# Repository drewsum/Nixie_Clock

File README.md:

# Nixie_Clock

Rev B Hardware designed with KiCad 7.0.1

Rev B MCU Firmware written with MPLAB X IDE v6.15, compiled with Microchip XC32 2.30 Compiler - NOT COMPATIBLE with newer compiler versions (4.30)

## Rev A Readme:
A nixie clock designed around a PIC16LF1519

Programming notes: PIC16LF1519 (U501) is programmed through PICKIT3 interface header (J501). Firmware included in GIT repository should already be built and the hex file can be programmed directly into the flash on the PIC. If you wish to build it yourself, use Microchip's XC8 compiler, and ensure that the User ID bytes located in NVM match the expected_user_ID[] byte array saved in RAM. The values programmed into NVM are set in /mcc_generated_files/mcc.c, and are set with the line #pragma config IDLOCx = _ . Reference page 44 of the PIC16LF1519 datasheet. If you don't feel like altering user ID's, leave them unchanged in source code, and just build it as is. If user IDs and device IDs do not match, the clock will brick itself until reprogrammed with matching values.

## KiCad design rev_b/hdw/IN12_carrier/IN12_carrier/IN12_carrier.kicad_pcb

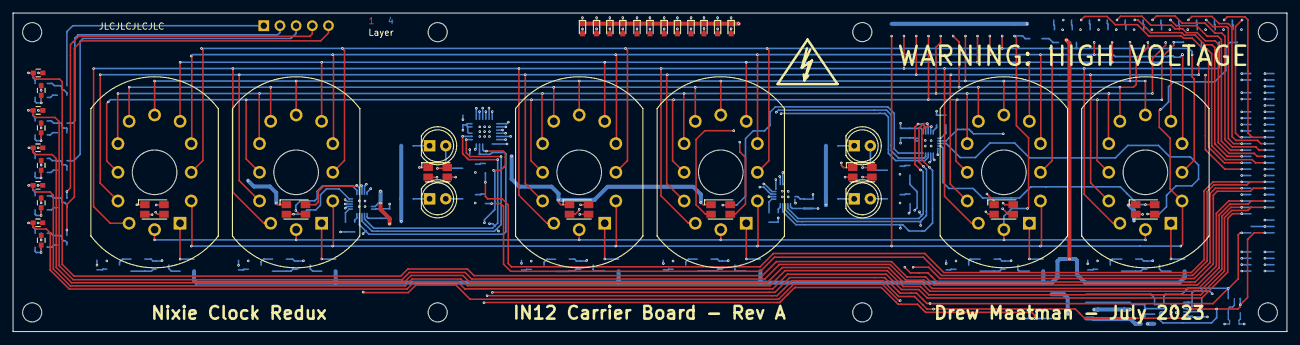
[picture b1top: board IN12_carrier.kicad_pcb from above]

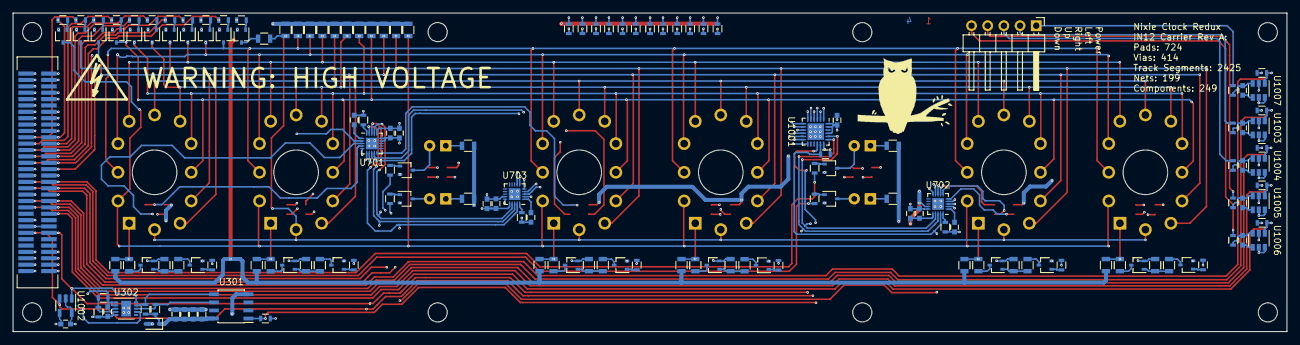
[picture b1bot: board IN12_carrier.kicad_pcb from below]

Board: 4 copper layers, 200.0 x 50.0 mm, 203 parts (155 on the bottom side), 172 nets.

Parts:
C301, C302, C303, C701, C702, C703, C704, C705, C706: 10uF; C_0603
C304, C305, C707, C708, C709, C1001, C1002, C1003, C1004, C1005, C1006, C1011, C1012, C1013, C1014, C1015, C1017: 0.1uF; C_0603
C1007, C1008, C1009, C1010, C1016: 10nF; C_0603
D301: BAT48JFILM; D_SOD-323
D701, D702, D703, D704, D705, D706, D707, D708: ASMB-MTB0-0A3A2; LED_Avago_PLCC4_3.2x2.8mm_CW
D901, D1001, D1002, D1003, D1004, D1005, D1006, D1007, D1008, D1009, D1010, D1011: Orange; LED_0603
H1201, H1202, H1203, H1204, H1205, H1206, H1207, H1208: MountingHole; MountingHole_3mm
J201: Conn_02x32_Top_Bottom; CONN_5120528-1_TYC
J1001: Cap SNS; PinHeader_1x05_P2.54mm_Horizontal
Q401, Q402, Q403, Q407, Q408, Q409, Q501, Q502, Q503, Q504, Q505, Q506, Q507, Q508, Q509, Q510, Q511, Q512, Q513, Q514, Q515: MMSTA42; SOT-323_SC-70
Q404, Q405, Q406, Q410, Q411, Q412: MMSTA92; SOT-323_SC-70
R301, R302, R305, R401, R402, R403, R413, R414, R415, R501, R502, R503, R504, R505, R506, R507, R508, R509, R510, R511, R512, R513, R515, R516, R701, R1012, R1013, R1014, R1015, R1020: 10k; R_0603
R303: 392k; R_0603
R304: 1M; R_0603
R404, R405, R406, R416, R417, R418, R801, R802, R803, R804, R805, R806, R807, R808, R809, R810, R811, R812, R813, R814, R815, R816, R817: 470k; R_0805
R407, R408, R409, R419, R420, R421: 100k; R_0805
R410, R411, R412, R422, R423, R424, R514: 18k; R_0805
R601, R602, R603, R604: 10k; R_0805
R704, R705, R706: 3.65k; R_0603
R901, R1001, R1002, R1003, R1004, R1005, R1006, R1007, R1008, R1009, R1010, R1011, R1016, R1017, R1018, R1019, R1021: 499; R_0603
U301: DS1683; SOIC-8_3.9x4.9mm_Pitch1.27mm
U302: LTC4316DD; DFN-10-1EP_3x3mm_Pitch0.5mm
U701, U702, U703: LP5009; UQFN-20-1EP_3x3mm_Pitch0.4mm
U1001: TCA9555RGER; QFN-24-1EP_4x4mm_P0.5mm_EP2.6x2.6mm
U1002: 24AA02-OT; SOT-23-5
U1003, U1004, U1005, U1006, U1007: AT42QT1010-TSHR; SOT-23-6
V601, V602, V603, V604, V605, V608: IN12B; IN-12B
V606, V607, V609, V610: IN3; LED_D5.0mm

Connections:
24HR_Mode_LED: R1010.1, U1001.11
+3.3V: C305.1, C704.1, C705.1, C706.1, C707.1, C708.1, C709.1, C1001.1, C1002.1, C1011.1, C1012.1, C1013.1, C1014.1, C1017.1, D301.2 (A), D701.1 (A), D702.1 (A), D703.1 (A), D704.1 (A), D705.1 (A), D706.1 (A), D707.1 (A), D708.1 (A), J201.61, J201.62, J201.63, J201.64, R304.1, U302.4 (VCC), U302.5 (Enable), U701.16 (VCC), U702.14 (ADDR0), U702.16 (VCC), U703.15 (ADDR1), U703.16 (VCC), U1001.18 (A0), U1001.21 (VCC), U1001.23 (A1), U1001.24 (A2), U1002.4 (V_{CC}), U1003.5 (VDD), U1003.6 (SYNC), U1004.5 (VDD), U1004.6 (SYNC), U1005.5 (VDD), U1005.6 (SYNC), U1006.5 (VDD), U1006.6 (SYNC), U1007.5 (VDD), U1007.6 (SYNC)
+90V: J201.33, J201.34, R801.2, R802.2, R803.2, R804.2, R805.2, R806.2, R807.2, R808.2, R809.2, R810.2, R811.2, R812.2, R813.2, R814.2, R815.2, R816.2, R817.2
+180V: J201.36, J201.37, Q404.2 (E), Q405.2 (E), Q406.2 (E), Q410.2 (E), Q411.2 (E), Q412.2 (E), R407.2, R408.2, R409.2, R419.2, R420.2, R421.2, R601.1, R602.1, R603.1, R604.1
Alarm_Enable_LED: R1009.1, U1001.10
Anode_0: R410.1, R801.1, V604.1 (Anode)
Anode_0_DSP: J201.39, R401.1
Anode_1: R422.1, R802.1, V602.1 (Anode)
Anode_1_DSP: J201.7, R413.1
Anode_2: R411.1, R803.1, V608.1 (Anode)
Anode_2_DSP: J201.40, R402.1
Anode_3: R423.1, R804.1, V605.1 (Anode)
Anode_3_DSP: J201.8, R414.1
Anode_4: R412.1, R805.1, V603.1 (Anode)
Anode_4_DSP: J201.41, R403.1
Anode_5: R424.1, R806.1, V601.1 (Anode)
Anode_5_DSP: J201.9, R415.1
COLON0_LED_B: D703.2 (BK), U703.4 (OUT2)
COLON0_LED_G: D703.3 (GK), U703.3 (OUT1)
COLON0_LED_R: D703.4 (RK), U703.2 (OUT0)
COLON1_LED_B: D706.2 (BK), U703.7 (OUT5)
COLON1_LED_G: D706.3 (GK), U703.6 (OUT4)
COLON1_LED_R: D706.4 (RK), U703.5 (OUT3)
Cathode_0: Q501.3 (C), R807.1, V601.2 (Digit0), V602.2 (Digit0), V603.2 (Digit0), V604.2 (Digit0), V605.2 (Digit0), V608.2 (Digit0)
Cathode_0_DSP: J201.43, R501.1
Cathode_1: Q506.3 (C), R808.1, V601.11 (Digit1), V602.11 (Digit1), V603.11 (Digit1), V604.11 (Digit1), V605.11 (Digit1), V608.11 (Digit1)
Cathode_1_DSP: J201.11, R506.1
Cathode_2: Q502.3 (C), R809.1, V601.10 (Digit2), V602.10 (Digit2), V603.10 (Digit2), V604.10 (Digit2), V605.10 (Digit2), V608.10 (Digit2)
Cathode_2_DSP: J201.44, R502.1
Cathode_3: Q507.3 (C), R810.1, V601.9 (Digit3), V602.9 (Digit3), V603.9 (Digit3), V604.9 (Digit3), V605.9 (Digit3), V608.9 (Digit3)
Cathode_3_DSP: J201.12, R507.1
Cathode_4: Q503.3 (C), R811.1, V601.8 (Digit4), V602.8 (Digit4), V603.8 (Digit4), V604.8 (Digit4), V605.8 (Digit4), V608.8 (Digit4)
Cathode_4_DSP: J201.45, R503.1
Cathode_5: Q508.3 (C), R812.1, V601.7 (Digit5), V602.7 (Digit5), V603.7 (Digit5), V604.7 (Digit5), V605.7 (Digit5), V608.7 (Digit5)
Cathode_5_DSP: J201.13, R508.1
Cathode_6: Q504.3 (C), R813.1, V601.6 (Digit6), V602.6 (Digit6), V603.6 (Digit6), V604.6 (Digit6), V605.6 (Digit6), V608.6 (Digit6)
Cathode_6_DSP: J201.46, R504.1
Cathode_7: Q509.3 (C), R814.1, V601.5 (Digit7), V602.5 (Digit7), V603.5 (Digit7), V604.5 (Digit7), V605.5 (Digit7), V608.5 (Digit7)
Cathode_7_DSP: J201.14, R509.1
Cathode_8: Q505.3 (C), R815.1, V601.4 (Digit8), V602.4 (Digit8), V603.4 (Digit8), V604.4 (Digit8), V605.4 (Digit8), V608.4 (Digit8)
Cathode_8_DSP: J201.47, R505.1
Cathode_9: Q510.3 (C), R816.1, V601.3 (Digit9), V602.3 (Digit9), V603.3 (Digit9), V604.3 (Digit9), V605.3 (Digit9), V608.3 (Digit9)
Cathode_9_DSP: J201.15, R510.1
Cathode_DP: R514.2, R817.1, V601.12 (DP), V602.12 (DP), V603.12 (DP), V604.12 (DP), V605.12 (DP), V608.12 (DP)
Cathode_DP_DSP: J201.48, R511.1
Colon_0_Cathode: Q513.3 (C), V606.2 (Kathode)
Colon_0_DSP: J201.50, R513.1
Colon_1_Cathode: Q512.3 (C), V607.2 (Kathode)
Colon_1_DSP: J201.18, R512.1
Colon_2_Cathode: Q515.3 (C), V609.2 (Kathode)
Colon_2_DSP: J201.51, R516.1
Colon_3_Cathode: Q514.3 (C), V610.2 (Kathode)
Colon_3_DSP: J201.19, R515.1
Display_Alarm_LED: R1007.1, U1001.7 (P06)
Display_Date_LED: R1003.1, U1001.3 (P02)
Display_Time_LED: R1001.1, U1001.1 (P00)
Display_Weekday_LED: R1005.1, U1001.5 (P04)
GND: C301.2, C302.2, C303.2, C304.2, C305.2, C701.2, C702.2, C703.2, C704.2, C705.2, C706.2, C707.2, C708.2, C709.2, C1001.2, C1002.2, C1003.2, C1004.2, C1005.2, C1006.2, C1011.2, C1012.2, C1013.2, C1014.2, C1015.2, C1017.2, D901.1 (K), D1001.1 (K), D1002.1 (K), D1003.1 (K), D1004.1 (K), D1005.1 (K), D1006.1 (K), D1007.1 (K), D1008.1 (K), D1009.1 (K), D1010.1 (K), D1011.1 (K), J201.1, J201.2, J201.3, J201.4, J201.5, J201.6, J201.10, J201.16, J201.17, J201.20, J201.24, J201.25, J201.29, J201.30, J201.31, J201.32, J201.42, J201.49, J201.52, J201.57, Q401.2 (E), Q402.2 (E), Q403.2 (E), Q407.2 (E), Q408.2 (E), Q409.2 (E), Q501.2 (E), Q502.2 (E), Q503.2 (E), Q504.2 (E), Q505.2 (E), Q506.2 (E), Q507.2 (E), Q508.2 (E), Q509.2 (E), Q510.2 (E), Q511.2 (E), Q512.2 (E), Q513.2 (E), Q514.2 (E), Q515.2 (E), R303.2, R305.2, R701.2, R704.2, R705.2, R706.2, R1012.2, R1013.2, R1014.2, R1015.2, R1020.2, U301.4 (GND), U302.1 (GND), U302.2 (XORH), U302.11 (GND), U701.14 (ADDR0), U701.15 (ADDR1), U701.21 (GND), U702.15 (ADDR1), U702.21 (GND), U703.14 (ADDR0), U703.21 (GND), U1001.9 (GND), U1001.25 (EPAD), U1002.2 (V_{SS}), U1002.5 (WP), U1003.2 (VSS), U1004.2 (VSS), U1005.2 (VSS), U1006.2 (VSS), U1007.2 (VSS)
I2C_DSP_SCL: J201.58, U302.10 (SCLIN), U701.18 (SCL), U702.18 (SCL), U703.18 (SCL), U1001.19 (SCL), U1002.1 (SCL)
I2C_DSP_SDA: J201.26, U302.7 (SDAIN), U701.17 (SDA), U702.17 (SDA), U703.17 (SDA), U1001.20 (SDA), U1002.3 (SDA)
unnamed: C301.1, C302.1, C303.1, C304.1, D301.1 (K), R301.1, R302.1, U301.8 (VCC)
unnamed: D901.2 (A), R901.2
unnamed: D1001.2 (A), R1001.2
unnamed: D1002.2 (A), R1002.2
unnamed: D1003.2 (A), R1003.2
unnamed: D1004.2 (A), R1004.2
unnamed: D1005.2 (A), R1005.2
unnamed: D1006.2 (A), R1006.2
unnamed: D1007.2 (A), R1007.2
unnamed: D1008.2 (A), R1008.2
unnamed: D1009.2 (A), R1009.2
unnamed: D1010.2 (A), R1010.2
unnamed: D1011.2 (A), R1011.2
unnamed: Q401.1 (B), R401.2
unnamed: Q401.3 (C), R404.1
unnamed: Q402.1 (B), R402.2
unnamed: Q402.3 (C), R405.1
unnamed: Q403.1 (B), R403.2
unnamed: Q403.3 (C), R406.1
unnamed: Q404.1 (B), R404.2, R407.1
unnamed: Q404.3 (C), R410.2
unnamed: Q405.1 (B), R405.2, R408.1
unnamed: Q405.3 (C), R411.2
unnamed: Q406.1 (B), R406.2, R409.1
unnamed: Q406.3 (C), R412.2
unnamed: Q407.1 (B), R413.2
unnamed: Q407.3 (C), R416.1
unnamed: Q408.1 (B), R414.2
unnamed: Q408.3 (C), R417.1
unnamed: Q409.1 (B), R415.2
unnamed: Q409.3 (C), R418.1
unnamed: Q410.1 (B), R416.2, R419.1
unnamed: Q410.3 (C), R422.2
unnamed: Q411.1 (B), R417.2, R420.1
unnamed: Q411.3 (C), R423.2
unnamed: Q412.1 (B), R418.2, R421.1
unnamed: Q412.3 (C), R424.2
unnamed: Q501.1 (B), R501.2
unnamed: Q502.1 (B), R502.2
unnamed: Q503.1 (B), R503.2
unnamed: Q504.1 (B), R504.2
unnamed: Q505.1 (B), R505.2
unnamed: Q506.1 (B), R506.2
unnamed: Q507.1 (B), R507.2
unnamed: Q508.1 (B), R508.2
unnamed: Q509.1 (B), R509.2
unnamed: Q510.1 (B), R510.2
unnamed: Q511.1 (B), R511.2
unnamed: Q511.3 (C), R514.1
unnamed: Q512.1 (B), R512.2
unnamed: Q513.1 (B), R513.2
unnamed: Q514.1 (B), R515.2
unnamed: Q515.1 (B), R516.2
unnamed: R301.2, U301.5 (SCL), U302.9 (SCLOUT)
unnamed: R302.2, U301.6 (SDA), U302.8 (SDAOUT)
unnamed: R303.1, R304.2, U302.3 (XORL)
unnamed: R704.1, U701.20 (IREF)
unnamed: C701.1, U701.1 (VCAP)
unnamed: R705.1, U702.20 (IREF)
unnamed: C702.1, U702.1 (VCAP)
unnamed: R706.1, U703.20 (IREF)
unnamed: C703.1, U703.1 (VCAP)
unnamed: C1007.1, U1003.4 (SNS)
unnamed: C1007.2, R1016.2, U1003.3 (SNSK)
unnamed: C1008.1, U1004.4 (SNS)
unnamed: C1008.2, R1017.2, U1004.3 (SNSK)
unnamed: C1009.1, U1005.4 (SNS)
unnamed: C1009.2, R1018.2, U1005.3 (SNSK)
unnamed: C1010.1, U1006.4 (SNS)
unnamed: C1010.2, R1019.2, U1006.3 (SNSK)
unnamed: C1016.1, U1007.4 (SNS)
unnamed: C1016.2, R1021.2, U1007.3 (SNSK)
unnamed: R601.2, V606.1 (Anode)
unnamed: R602.2, V607.1 (Anode)
unnamed: R603.2, V609.1 (Anode)
unnamed: R604.2, V610.1 (Anode)
Pushbutton_Down: C1005.1, J201.55, R1014.1, U1006.1 (OUT)
Pushbutton_Down_SNS: J1001.5, R1019.1
Pushbutton_Left: C1015.1, J201.21, R1020.1, U1003.1 (OUT)
Pushbutton_Left_SNS: J1001.2, R1016.1
Pushbutton_Power: C1006.1, J201.53, R1015.1, U1007.1 (OUT)
Pushbutton_Power_SNS: J1001.1, R1021.1
Pushbutton_Right: C1003.1, J201.54, R1012.1, U1004.1 (OUT)
Pushbutton_Right_SNS: J1001.3, R1017.1
Pushbutton_Up: C1004.1, J201.22, R1013.1, U1005.1 (OUT)
Pushbutton_Up_SNS: J1001.4, R1018.1
Set_Alarm_LED: R1008.1, U1001.8 (P07)
Set_Brightness_LED: R1011.1, U1001.12
Set_Color_LED: R901.1, U1001.13
Set_Date_LED: R1004.1, U1001.4 (P03)
Set_Time_LED: R1002.1, U1001.2 (P01)
Set_Weekday_LED: R1006.1, U1001.6 (P05)
TUBE0_LED_B: D701.2 (BK), U701.4 (OUT2)
TUBE0_LED_G: D701.3 (GK), U701.3 (OUT1)
TUBE0_LED_R: D701.4 (RK), U701.2 (OUT0)
TUBE1_LED_B: D704.2 (BK), U701.7 (OUT5)
TUBE1_LED_G: D704.3 (GK), U701.6 (OUT4)
TUBE1_LED_R: D704.4 (RK), U701.5 (OUT3)
TUBE2_LED_B: D707.2 (BK), U701.10 (OUT8)
TUBE2_LED_G: D707.3 (GK), U701.9 (OUT7)
TUBE2_LED_R: D707.4 (RK), U701.8 (OUT6)
TUBE3_LED_B: D702.2 (BK), U702.4 (OUT2)
TUBE3_LED_G: D702.3 (GK), U702.3 (OUT1)
TUBE3_LED_R: D702.4 (RK), U702.2 (OUT0)
TUBE4_LED_B: D705.2 (BK), U702.7 (OUT5)
TUBE4_LED_G: D705.3 (GK), U702.6 (OUT4)
TUBE4_LED_R: D705.4 (RK), U702.5 (OUT3)
TUBE5_LED_B: D708.2 (BK), U702.10 (OUT8)
TUBE5_LED_G: D708.3 (GK), U702.9 (OUT7)
TUBE5_LED_R: D708.4 (RK), U702.8 (OUT6)
Tube_ETC_Enable: R305.1, U301.1 (EVENT), U1001.16
Tube_LED_Enable: R701.1, U701.19 (EN), U702.19 (EN), U703.19 (EN), U1001.17

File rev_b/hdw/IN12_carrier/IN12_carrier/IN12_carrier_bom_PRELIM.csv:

Component,Description,Part,References,Value,Configuration,Footprint,Quantity Per PCB,,,Digi-Key PN,Voltage,display_footprint,Footprint Display,Tolerance,Wattage
1,Unpolarized capacitor,C_Custom,C1007 C1008 C1009 C1010 C1016,10nF,,C_0603,5,,,1276-1009-1-ND,50V,603,,,
2,Unpolarized capacitor,C_Custom,C707 C708 C709 C1001 C1002 C1003 C1004 C1005 C1006 C1011 C1012 C1013 C1014 C1015 C1017,0.1uF,,C_0603,15,,,1276-CL10B104KB8NNNLCT-ND,50V,603,,,
3,,C_Custom,C304 C305,0.1uF,ETC,C_0603,2,,,1276-CL10B104KB8NNNLCT-ND,50V,603,,,
4,,C_Custom,C301 C302 C303,10uF,ETC,C_0603,3,,,1276-1871-1-ND,10V,603,,,
5,Unpolarized capacitor,C_Custom,C701 C702 C703 C704 C705 C706,10uF,,C_0603,6,,,1276-1871-1-ND,10V,603,,,
6,"Tricolor Black Surface LED, Common Anode Pin 1, PLCC-4",ASMB-MTB0-0A3A2,D701 D702 D703 D704 D705 D706 D707 D708,ASMB-MTB0-0A3A2,,LED_Avago_PLCC4_3.2x2.8mm_CW,8,,,516-3279-1-ND,,,,,
7,Light emitting diode,LED,D901 D1001 D1002 D1003 D1004 D1005 D1006 D1007 D1008 D1009 D1010 D1011,Amber,,LED_0603,12,,,732-150060AS75000CT-ND,,,,,
8,"40V 0.35A Small Signal Schottky Diode, SOD-323",BAT48JFILM,D301,BAT48JFILM,ETC,D_SOD-323,1,,,497-5711-1-ND,,,,,
,,,,,,,,,,,,,,,
,,,,,,,,,,,,,,,
,,,,,,,,,,,,,,,
,,,,,,,,,,,,,,,
,,,,,,,,,,,,,,,
,,,,,,,,,,,,,,,
,,,,,,,,,,,,,,,
16,"Generic connector, double row, 02x32, top/bottom pin numbering scheme (row 1: 1...pins_per_row, row2: pins_per_row+1 ... num_pins), script generated (kicad-library-utils/schlib/autogen/connector/)",Conn_02x32_Top_Bottom,J201,Conn_02x32_Top_Bottom,,CONN_5120528-1_TYC,1,,,A104089CT-ND,,,,,
17,,Screw,MK1107 MK1108 MK1115 MK1116 MK1123 MK1124 MK1131 MK1132 MK1133 MK1134 MK1135 MK1136 MK1137 MK1138 MK1139 MK1140,Screw,,,16,,,36-9900-ND,,,,,
18,,Standoff,MK1101 MK1102 MK1103 MK1104 MK1105 MK1106 MK1109 MK1110 MK1111 MK1112 MK1113 MK1114 MK1117 MK1118 MK1119 MK1120 MK1121 MK1122 MK1125 MK1126 MK1127 MK1128 MK1129 MK1130,Standoff,,,24,,,1772-2080-ND 1772-1220-ND,,,,,
19,,Q_NPN_BEC,Q401 Q402 Q403 Q407 Q408 Q409 Q501 Q502 Q503 Q504 Q505 Q506 Q507 Q508 Q509 Q510 Q511 Q512 Q513 Q514 Q515,MMSTA42,,SOT-323_SC-70,21,,,MMSTA42-FDICT-ND,,,SOT-323,,
20,,Q_PNP_BEC,Q404 Q405 Q406 Q410 Q411 Q412,MMSTA92,,SOT-323_SC-70,6,,,MMSTA92-TPCT-ND,,,SOT-323,,
21,Resistor,R_Custom,R901 R1001 R1002 R1003 R1004 R1005 R1006 R1007 R1008 R1009 R1010 R1011 R1016 R1017 R1018 R1019 R1021,499,,R_0603,17,,,541-CRCW0603499RFKEBCT-ND,,603,,1%,1/10W
22,Resistor,R_Custom,R704 R705 R706,3.65k,,R_0603,3,,,541-3.65KHCT-ND,,603,,1%,1/10W
23,Resistor,R_Custom,R701 R1012 R1013 R1014 R1015 R1020,10k,,R_0603,6,,,541-10.0KHCT-ND,,603,,1%,1/10W
24,Resistor,R_Custom,R301 R302 R305,10k,ETC,R_0603,3,,,541-10.0KHCT-ND,,603,,1%,1/10W
25,Resistor,R_Custom,R401 R402 R403 R413 R414 R415 R501 R502 R503 R504 R505 R506 R507 R508 R509 R510 R511 R512 R513 R515 R516,10k,,R_0603,21,,,541-10.0KHCT-ND,,603,,1%,1/10W
26,,R,R601 R602 R603 R604,10k,,R_0805,4,,,541-3015-1-ND,,805,,1%,1/10W
27,Resistor,R_Custom,R410 R411 R412 R422 R423 R424 R514,18k,,R_0805,7,,,541-18.0KCCT-ND,,805,,1%,1/8W
28,Resistor,R_Custom,R407 R408 R409 R419 R420 R421,100k,,R_0805,6,,,541-4318-1-ND,,805,,1%,1/8W
29,Resistor,R_Custom,R303,392k,ETC,R_0603,1,,,541-392KHCT-ND,,603,,1%,1/10W
30,Resistor,R_Custom,R404 R405 R406 R416 R417 R418 R801 R802 R803 R804 R805 R806 R807 R808 R809 R810 R811 R812 R813 R814 R815 R816 R817,470k,,R_0805,23,,,541-470KCCT-ND Digi-Key PN: 541-470KCCT-ND,,805,,1%,1/8W
31,Resistor,R_Custom,R304,1M,ETC,R_0603,1,,,541-2990-1-ND,,603,,1%,1/10W
32,"I2C Serial EEPROM, 2Kb, SOT-23",24AA02-OT,U1002,24AA02-OT,,SOT-23-5,1,,,24AA02E64T-I/OT,,,,,
33,"Single-key Touch Sensor, SOT-23-6",AT42QT1010-TSHR,U1003 U1004 U1005 U1006 U1007,AT42QT1010-TSHR,,SOT-23-6,5,,,AT42QT1010-TSHRCT-ND,,,,,
34,,DS1683,U301,DS1683,ETC,SOIC-8_3.9x4.9mm_Pitch1.27mm,1,,,DS1683S+-ND,,,,,
35,"LP50xx 9-Channel, 12-Bit PWM Ultra-low Quiescent Current I2C RGB LED Drivers",LP5009,U701 U702 U703,LP5009,,UQFN-20-1EP_3x3mm_Pitch0.4mm,3,,,296-LP5009RUKRCT-ND,,,,,
36,Single I2C/SMBUS Address Translator,LTC4316DD,U302,LTC4316DD,ETC,DFN-10-1EP_3x3mm_Pitch0.5mm,1,,,LTC4316IDD#PBF-ND,,,,,
37,"16-bit I/O expander, I2C and SMBus interface, interrupts, w/ pull-ups, QFN-24",TCA9555RGER,U1001,TCA9555RGER,,QFN-24-1EP_4x4mm_P0.5mm_EP2.6x2.6mm,1,,,296-44537-1-ND,,,,,
38,,IN12B,V601 V602 V603 V604 V605 V608,IN12B,,IN-12B,6,,,,,,,,
39,,IN3,V606 V607 V609 V610,IN3,,LED_D5.0mm,4,,,,,,,,

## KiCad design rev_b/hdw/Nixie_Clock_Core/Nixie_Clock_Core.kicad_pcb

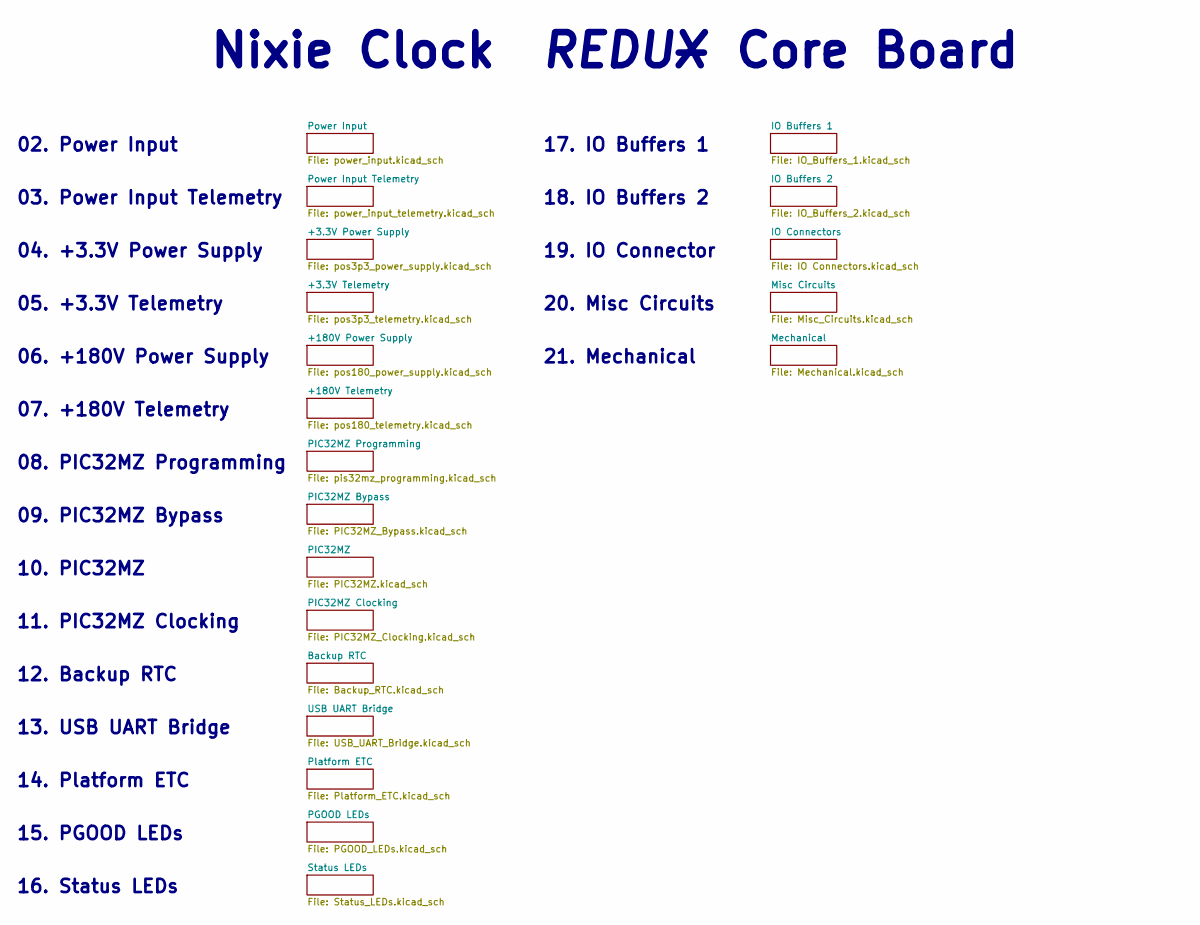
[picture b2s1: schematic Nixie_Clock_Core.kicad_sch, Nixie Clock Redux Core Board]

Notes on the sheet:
04. +3.3V Power Supply
Nixie Clock - Core Board
12. Backup RTC
20. Misc Circuits
02. Power Input
11. PIC32MZ Clocking
09. PIC32MZ Bypass
06. +180V Power Supply
17. IO Buffers 1
08. PIC32MZ Programming
07. +180V Telemetry
13. USB UART Bridge
16. Status LEDs
15. PGOOD LEDs
REDUX
21. Mechanical
18. IO Buffers 2
05. +3.3V Telemetry
14. Platform ETC
03. Power Input Telemetry
19. IO Connector
10. PIC32MZ

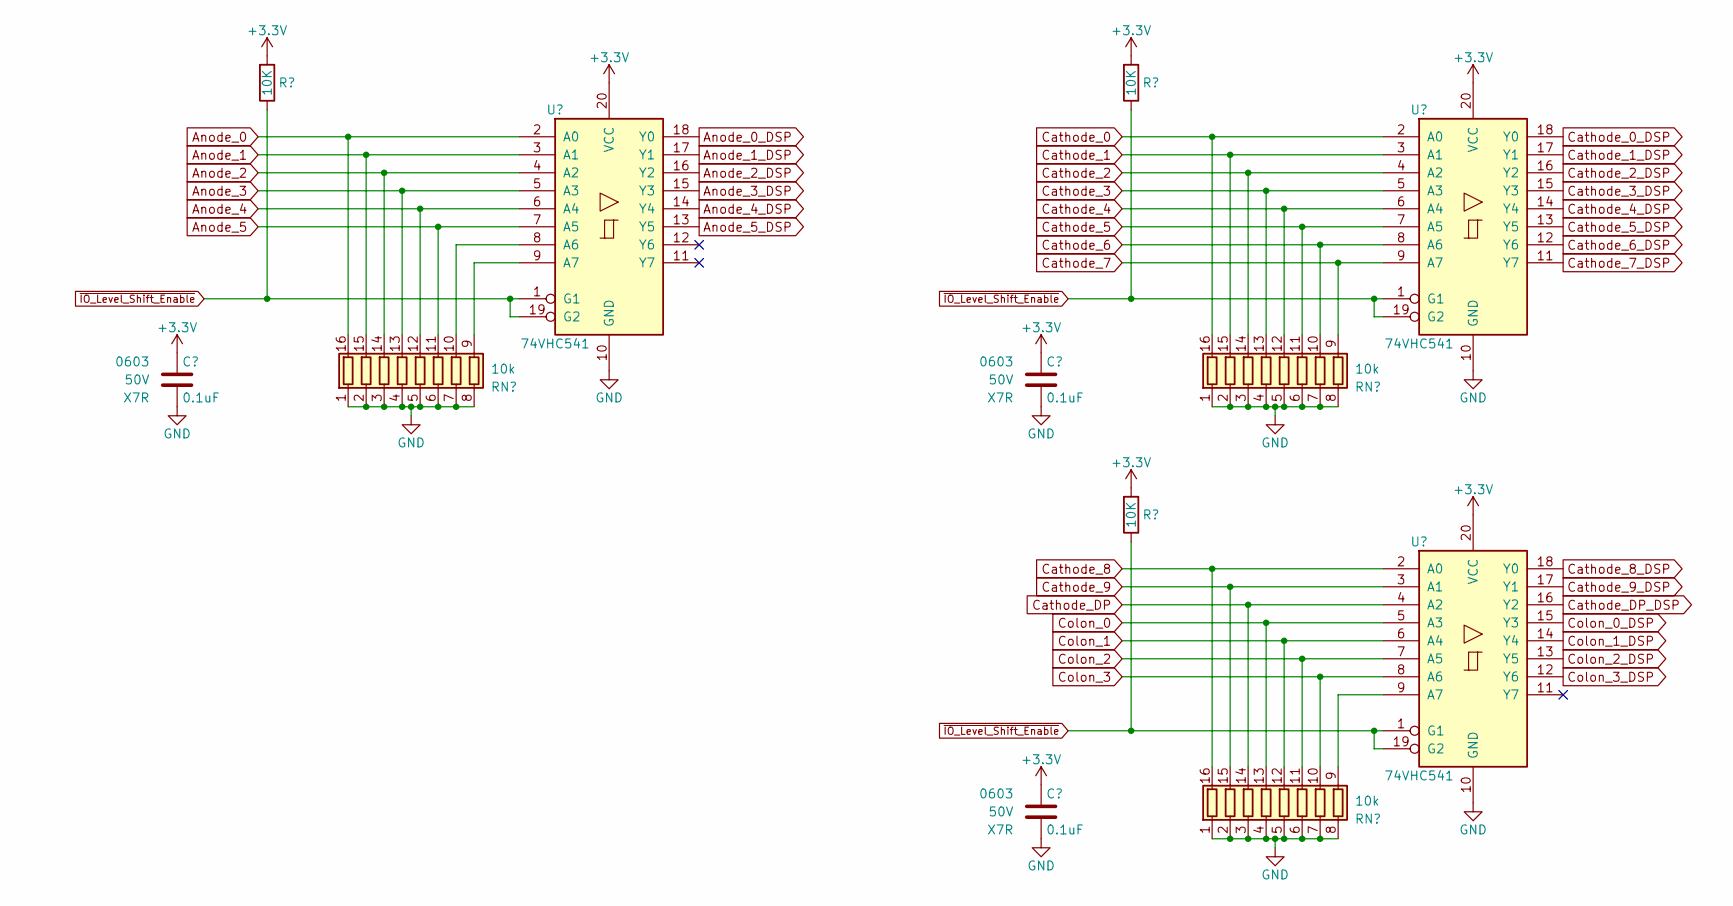
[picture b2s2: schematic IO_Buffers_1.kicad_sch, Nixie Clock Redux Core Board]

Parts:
C1701, C1702, C1703: 0.1uF; C_0603; Voltage 50V; Digi-Key PN 1276-1935-1-ND
R1701, R1702, R1703: 10K; R_0603; Tolerance 1%; Digi-Key PN 541-10.0KHCT-ND
RN1701, RN1702, RN1703: 10k; R_Array_Convex_8x0602; Tolerance 1%; Digi-Key PN Y1103CT-ND
U1701, U1702, U1703: 74VHC541; WQFN-20-1EP_2.5x4.5mm_P0.5mm_EP1x2.9mm; Digi-Key PN 1727-7068-1-ND

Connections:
Anode_0: RN1701.16 (R1.2), U1701.2 (A0); also elsewhere on the board
Anode_0_DSP: U1701.18 (Y0); also elsewhere on the board
Anode_1: RN1701.15 (R2.2), U1701.3 (A1); also elsewhere on the board
Anode_1_DSP: U1701.17 (Y1); also elsewhere on the board
Anode_2: RN1701.14 (R3.2), U1701.4 (A2); also elsewhere on the board
Anode_2_DSP: U1701.16 (Y2); also elsewhere on the board
Anode_3: RN1701.13 (R4.2), U1701.5 (A3); also elsewhere on the board
Anode_3_DSP: U1701.15 (Y3); also elsewhere on the board
Anode_4: RN1701.12 (R5.2), U1701.6 (A4); also elsewhere on the board
Anode_4_DSP: U1701.14 (Y4); also elsewhere on the board
Anode_5: RN1701.11 (R6.2), U1701.7 (A5); also elsewhere on the board
Anode_5_DSP: U1701.13 (Y5); also elsewhere on the board
Cathode_0: RN1702.16 (R1.2), U1702.2 (A0); also elsewhere on the board
Cathode_0_DSP: U1702.18 (Y0); also elsewhere on the board
Cathode_1: RN1702.15 (R2.2), U1702.3 (A1); also elsewhere on the board
Cathode_1_DSP: U1702.17 (Y1); also elsewhere on the board
Cathode_2: RN1702.14 (R3.2), U1702.4 (A2); also elsewhere on the board
Cathode_2_DSP: U1702.16 (Y2); also elsewhere on the board
Cathode_3: RN1702.13 (R4.2), U1702.5 (A3); also elsewhere on the board
Cathode_3_DSP: U1702.15 (Y3); also elsewhere on the board
Cathode_4: RN1702.12 (R5.2), U1702.6 (A4); also elsewhere on the board
Cathode_4_DSP: U1702.14 (Y4); also elsewhere on the board
Cathode_5: RN1702.11 (R6.2), U1702.7 (A5); also elsewhere on the board
Cathode_5_DSP: U1702.13 (Y5); also elsewhere on the board
Cathode_6: RN1702.10 (R7.2), U1702.8 (A6); also elsewhere on the board
Cathode_6_DSP: U1702.12 (Y6); also elsewhere on the board
Cathode_7: RN1702.9 (R8.2), U1702.9 (A7); also elsewhere on the board
Cathode_7_DSP: U1702.11 (Y7); also elsewhere on the board
Cathode_8: RN1703.16 (R1.2), U1703.2 (A0); also elsewhere on the board
Cathode_8_DSP: U1703.18 (Y0); also elsewhere on the board
Cathode_9: RN1703.15 (R2.2), U1703.3 (A1); also elsewhere on the board
Cathode_9_DSP: U1703.17 (Y1); also elsewhere on the board
Cathode_DP: RN1703.14 (R3.2), U1703.4 (A2); also elsewhere on the board
Cathode_DP_DSP: U1703.16 (Y2); also elsewhere on the board
Colon_0: RN1703.13 (R4.2), U1703.5 (A3); also elsewhere on the board
Colon_0_DSP: U1703.15 (Y3); also elsewhere on the board
Colon_1: RN1703.12 (R5.2), U1703.6 (A4); also elsewhere on the board
Colon_1_DSP: U1703.14 (Y4); also elsewhere on the board
Colon_2: RN1703.11 (R6.2), U1703.7 (A5); also elsewhere on the board
Colon_2_DSP: U1703.13 (Y5); also elsewhere on the board
Colon_3: RN1703.10 (R7.2), U1703.8 (A6); also elsewhere on the board
Colon_3_DSP: U1703.12 (Y6); also elsewhere on the board
GND: C1701.2, C1702.2, C1703.2, RN1701.1 (R1.1), RN1701.2 (R2.1), RN1701.3 (R3.1), RN1701.4 (R4.1), RN1701.5 (R5.1), RN1701.6 (R6.1), RN1701.7 (R7.1), RN1701.8 (R8.1), RN1702.1 (R1.1), RN1702.2 (R2.1), RN1702.3 (R3.1), RN1702.4 (R4.1), RN1702.5 (R5.1), RN1702.6 (R6.1), RN1702.7 (R7.1), RN1702.8 (R8.1), RN1703.1 (R1.1), RN1703.2 (R2.1), RN1703.3 (R3.1), RN1703.4 (R4.1), RN1703.5 (R5.1), RN1703.6 (R6.1), RN1703.7 (R7.1), RN1703.8 (R8.1), U1701.10 (GND), U1701.21 (GND), U1702.10 (GND), U1702.21 (GND), U1703.10 (GND), U1703.21 (GND); also elsewhere on the board
unnamed: RN1701.10 (R7.2), U1701.8 (A6)
unnamed: RN1701.9 (R8.2), U1701.9 (A7)
unnamed: RN1703.9 (R8.2), U1703.9 (A7)
~IO_Level_Shift_Enable: R1701.2, R1702.2, R1703.2, U1701.1 (G1), U1701.19 (G2), U1702.1 (G1), U1702.19 (G2), U1703.1 (G1), U1703.19 (G2); also elsewhere on the board

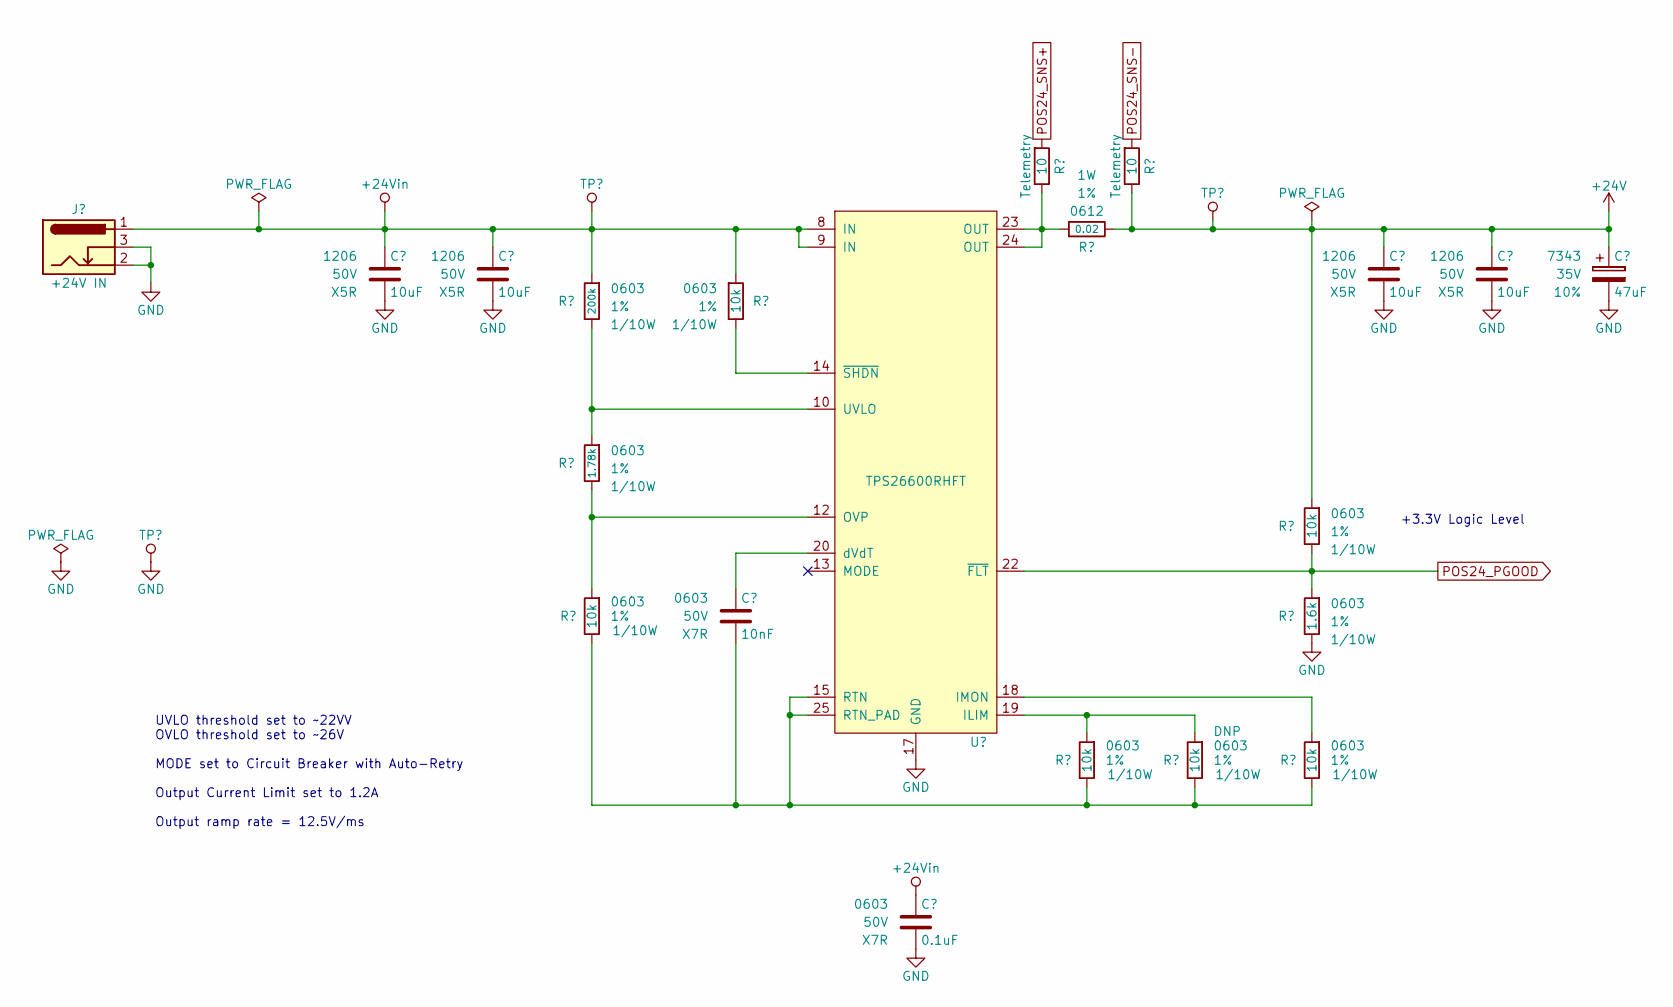
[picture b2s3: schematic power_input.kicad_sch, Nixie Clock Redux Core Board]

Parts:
C201, C202, C205, C206: 10uF; C_1206; Voltage 50V; Digi-Key PN 1276-6767-1-ND
C203: 10nF; C_0603; Voltage 50V; Digi-Key PN 1276-1009-1-ND
C204: 0.1uF; C_0603; Voltage 50V; Digi-Key PN 1276-1935-1-ND
C207: 47uF; CP_EIA-7343-43_Kemet-X; Voltage 35V; Tolerance 10%; Digi-Key PN 399-16639-1-ND
J201: +24V IN; BARREL_JACK
R201: 1.78k; R_0603; Tolerance 1%; Digi-Key PN 541-1.78KHCT-ND
R202: 200k; R_0603; Tolerance 1%; Digi-Key PN 541-4027-1-ND
R203, R204, R207, R209, R210, R212: 10k; R_0603; Tolerance 1%; Digi-Key PN 541-10.0KHCT-ND
R205, R208: 10; R_0603; Tolerance 1%; Digi-Key PN 541-10.0HCT-ND
R206: 0.02; R_0612; Tolerance 1%; Digi-Key PN P16010CT-ND
R211: 1.6k; R_0603; Tolerance 1%; Digi-Key PN 541-5237-1-ND
TP201: TP; PinHeader_1x01_P2.54mm_Horizontal
TP202, TP203: TP; Test_Point
U201: TPS26600RHFT; QFN-24-1EP_4x5mm_Pitch0.5mm; Digi-Key PN 296-45478-1-ND

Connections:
+24V: C205.1, C206.1, C207.1, R206.2, R208.2, R210.1, TP203.1 (TP); also elsewhere on the board
+24Vin: C201.1, C202.1, C204.1, J201.1, R202.1, R204.1, TP202.1 (TP), U201.8 (IN), U201.9 (IN)
GND: C201.2, C202.2, C204.2, C205.2, C206.2, C207.2, J201.2, J201.3, R211.2, TP201.1 (TP), U201.17 (GND); also elsewhere on the board
unnamed: R205.2, R206.1, U201.23 (OUT), U201.24 (OUT)
unnamed: R207.1, R209.1, U201.19 (ILIM)
unnamed: R212.1, U201.18 (IMON)
unnamed: R201.2, R203.1, U201.12 (OVP)
unnamed: C203.2, R203.2, R207.2, R209.2, R212.2, U201.15 (RTN), U201.25 (RTN_PAD)
unnamed: R201.1, R202.2, U201.10 (UVLO)
unnamed: C203.1, U201.20 (dVdT)
unnamed: R204.2, U201.14 (~SHDN)
POS24_PGOOD: R210.2, R211.1, U201.22 (~FLT); also elsewhere on the board
POS24_SNS+: R205.1; also elsewhere on the board
POS24_SNS-: R208.1; also elsewhere on the board

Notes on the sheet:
+3.3V Logic Level
UVLO threshold set to ~22VV OVLO threshold set to ~26V MODE set to Circuit Breaker with Auto-Retry Output Current Limit set to 1.2A Output ramp rate = 12.5V/ms

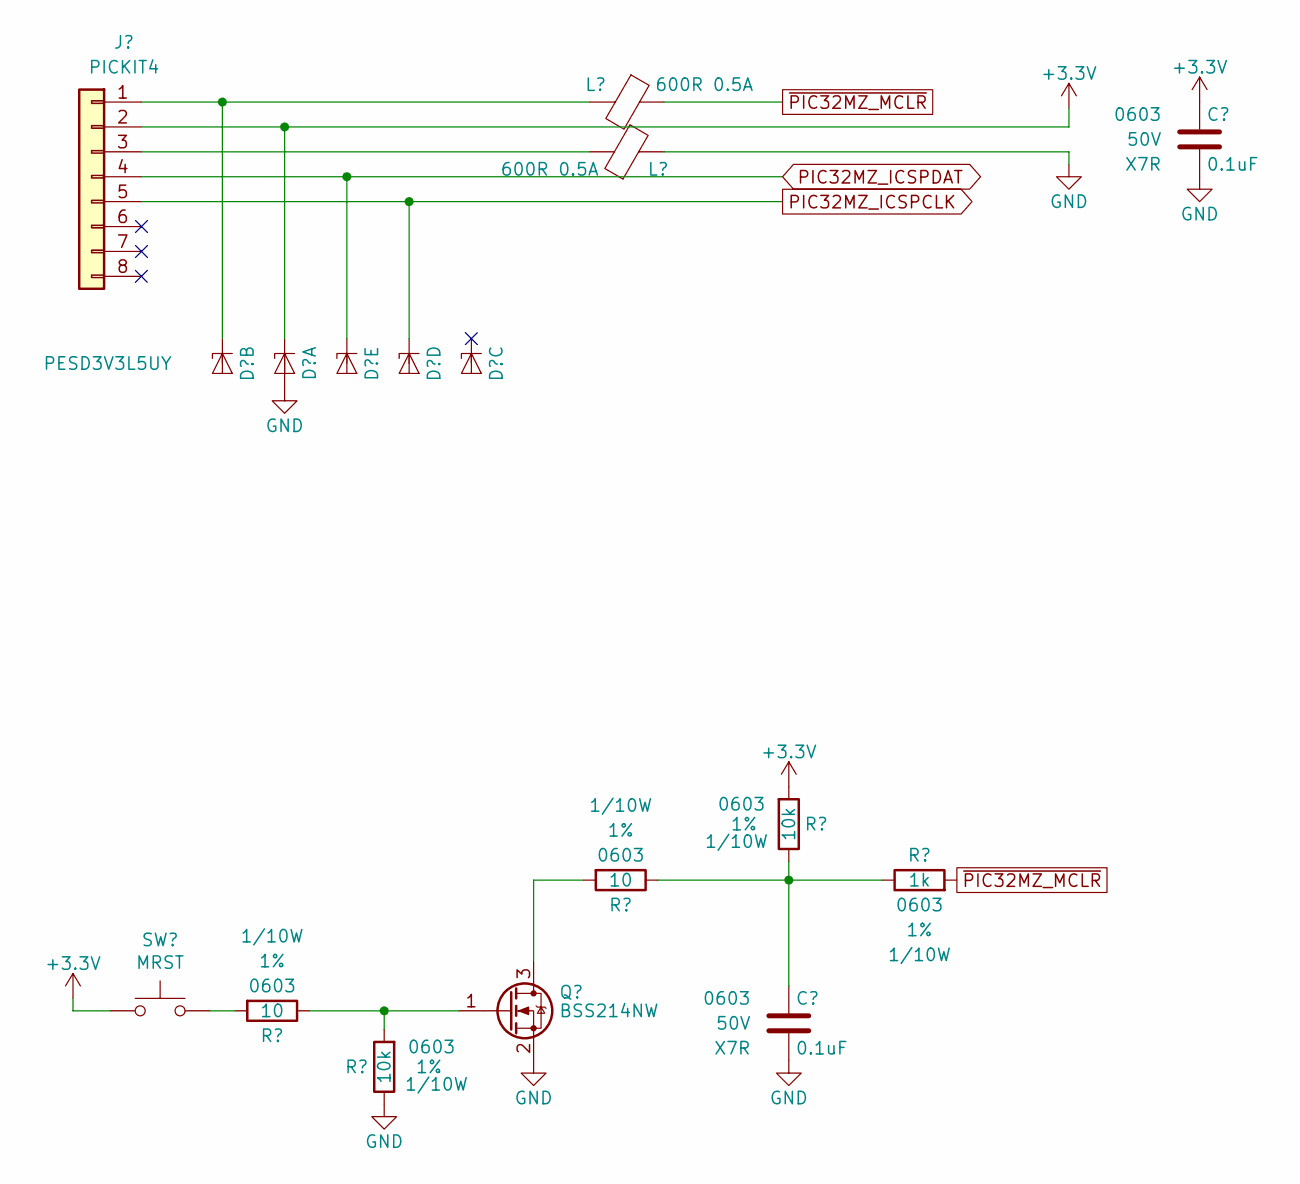
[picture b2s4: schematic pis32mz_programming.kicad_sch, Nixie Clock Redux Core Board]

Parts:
C801, C802: 0.1uF; C_0603; Voltage 50V; Digi-Key PN 1276-1935-1-ND
D801: PESD3V3L5UY; SOT-363_SC-70-6; Digi-Key PN 1727-3828-1-ND
J801: PICKIT4; PICKIT4_Header
L801, L802: 600R 0.5A; L_0603; Digi-Key PN 490-1014-1-ND
Q801: BSS214NW; SOT-323_SC-70; Digi-Key PN BSS214NWH6327XTSA1CT-ND
R801, R803: 10; R_0603; Tolerance 1%; Digi-Key PN 541-10.0HCT-ND
R802, R804: 10k; R_0603; Tolerance 1%; Digi-Key PN 541-10.0KHCT-ND
R805: 1k; R_0603; Tolerance 1%; Digi-Key PN 541-1.00KHCT-ND
SW801: MRST; SW_PUSH_6mm

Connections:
GND: C801.2, C802.2, D801.2 (A), L802.2, Q801.2 (S), R802.2; also elsewhere on the board
unnamed: C801.1, R803.2, R804.2, R805.2
unnamed: D801.3 (K2), J801.1, L801.2
unnamed: J801.3, L802.1
unnamed: Q801.3 (D), R803.1
unnamed: Q801.1 (G), R801.2, R802.1
unnamed: R801.1, SW801.2
PIC32MZ_ICSPCLK: D801.5 (K4), J801.5; also elsewhere on the board
PIC32MZ_ICSPDAT: D801.6 (K5), J801.4; also elsewhere on the board
~PIC32MZ_MCLR: L801.1, R805.1; also elsewhere on the board
